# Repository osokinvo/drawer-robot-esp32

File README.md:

# Drawer Robot (esp32)

Этот проект представляет собой робота, который может рисовать простые изображения на плоскости с помощью ESP32.

## 🔧 Особенности

- Управление шаговыми моторами
- Интеграция с FreeRTOS

## 🧩 Используемые технологии

- ESP32 + FreeRTOS
- KiCad для проектирования платы
- 3D-печать корпуса

## 🚀 Установка

1. Скопируйте репозиторий
2. Откройте `firmware/` в PlatformIO или ESP-IDF
3. Скомпилируйте и загрузите на ESP32

## 📂 Структура

- `hardware/pcb/` — разводка и схема платы
- `hardware/3d-models/` — детали корпуса
- `firmware/` — код прошивки
- `docs/` — изображения, схемы

## 📜 Лицензия

Проект распространяется под лицензией MIT.

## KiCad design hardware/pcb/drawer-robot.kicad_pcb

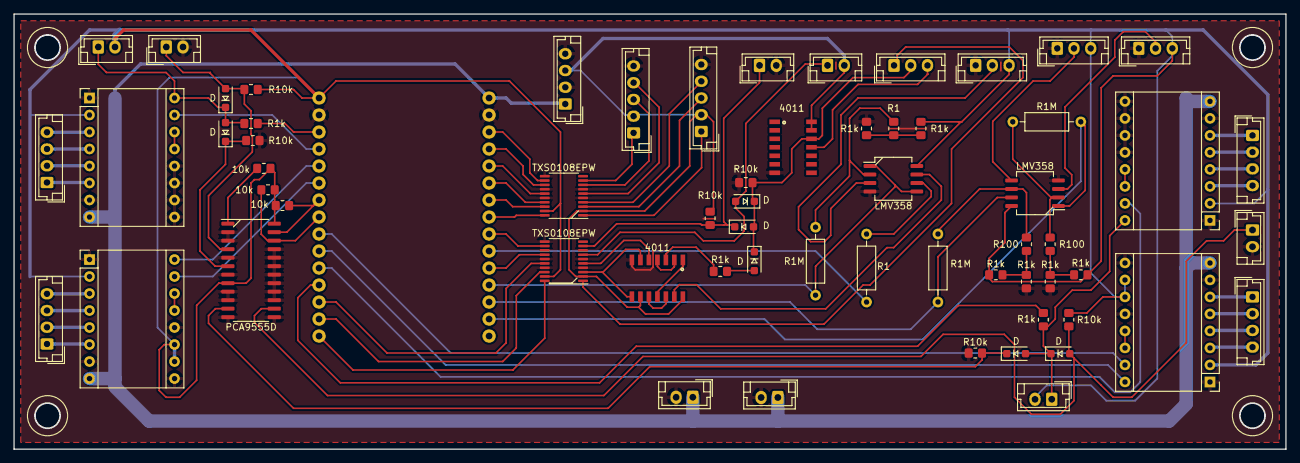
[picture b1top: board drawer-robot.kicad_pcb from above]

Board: 2 copper layers, 190.0 x 65.0 mm, 63 parts (0 on the bottom side), 85 nets.

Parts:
A1, A2, A3, A4: Pololu_Breakout_A4988; Pololu_Breakout-16_15.2x20.3mm
D1, D2, D3, D4, D5, D6, D7: D; D_SOD-123F_dir
J1: ESP32 WROOM DevKit v1
J2, J3, J5, J7, J10: Conn_01x04_Pin; JST_EH_B4B-EH-A_1x04_P2.50mm_Vertical
J4, J6, J8, J9, J11, J12, J22, J23: Conn_01x02_Pin; JST_EH_B2B-EH-A_1x02_P2.50mm_Vertical
J16, J17: Conn_01x05_Pin; JST_EH_B5B-EH-A_1x05_P2.50mm_Vertical
J18, J19, J20, J21: Conn_01x03_Pin; JST_EH_B3B-EH-A_1x03_P2.50mm_Vertical
R1, R3, R30, R31, R34, R35, R38, R39, R42: R1k; R_0805_2012Metric_Pad1.20x1.40mm_HandSolder
R2, R4, R5, R6, R43, R44: R10k; R_0805_2012Metric_Pad1.20x1.40mm_HandSolder
R7: R1; R_Axial_DIN0207_L6.3mm_D2.5mm_P10.16mm_Horizontal
R10, R11, R12: 10k; R_0805_2012Metric_Pad1.20x1.40mm_HandSolder
R32, R36: R100; R_0805_2012Metric_Pad1.20x1.40mm_HandSolder
R33, R37, R41: R1M; R_Axial_DIN0207_L6.3mm_D2.5mm_P10.16mm_Horizontal
R40: R1; R_0805_2012Metric_Pad1.20x1.40mm_HandSolder
U1, U3: LMV358; SO-8_5.3x6.2mm_P1.27mm
U4, U5: 4011; SOP14
U6: PCA9555D; SO-24_5.3x15mm_P1.27mm
U7, U8: TXS0108EPW; TSSOP-20_4.4x6.5mm_P0.65mm

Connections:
+5V: J10.3, J16.2, J17.2, J22.2, R44.2, U4.9, U4.14 (VDD), U5.13, U5.14 (VDD), U7.2 (VCCA), U8.2 (VCCA)
+12V: A1.8 (VMOT), A2.8 (VMOT), A3.8 (VMOT), A4.8 (VMOT), J1.1 (VIN), J10.1, J11.1, J12.1
A1: J1.7 (A9), U7.18 (B2)
A1_10k: J1.14 (VP), R33.1, U1.1
A2: J1.4 (GPIO12), U7.13 (B7)
A2_10k: J1.13 (VN), R37.1, U1.7
AZ_10M: J1.12 (A6), R41.1, U3.1, U3.5 (+)
B1: J1.8 (A8), U7.20 (B1)
B2: J1.3 (GPIO13), U7.12 (B8)
BRAKE_SD1_DIR: J1.18 (GPIO15), R3.1
BRAKE_SD1_STEP: A3.15 (STEP), J1.19 (GPIO2)
BRAKE_SD2_DIR: J1.27 (RX0), R1.1
BRAKE_SD2_STEP: A4.15 (STEP), J1.26 (GPIO21)
Clock2_Pin: J1.23 (GPIO5), R12.1, U6.22 (SCL)
Data2_Pin: J1.22 (TX2), R11.1, U6.23 (SDA)
EN_LOG_Z: J1.29 (GPIO22), U8.18 (B2)
EN_LOG_Z5V: U4.6, U4.8, U8.3 (A2)
FEEDBACK_Z5V: U3.7, U4.13
GND: A1.1 (GND), A1.7 (GND), A1.9 (~ENABLE), A1.12 (MS3), A2.1 (GND), A2.7 (GND), A2.9 (~ENABLE), A2.12 (MS3), A3.1 (GND), A3.7 (GND), A3.9 (~ENABLE), A3.10 (MS1), A3.11 (MS2), A3.12 (MS3), A4.1 (GND), A4.7 (GND), A4.9 (~ENABLE), A4.10 (MS1), A4.11 (MS2), A4.12 (MS3), J1.2 (GND), J1.17 (GND), J6.2, J9.2, J10.2, J10.4, J11.2, J12.2, J16.5, J17.5, J18.1, J19.1, J20.1, J23.2, R2.2, R5.2, R31.1, R35.1, R39.1, R43.2, U1.4 (V-), U3.4 (V-), U4.7 (VSS), U5.7 (VSS), U6.2 (A1), U6.3 (A2), U6.5 (IO0_1), U6.7 (IO0_3), U6.9 (IO0_5), U6.10 (IO0_6), U6.12 (VSS), U6.13 (IO1_0), U6.15 (IO1_2), U6.16 (IO1_3), U6.17 (IO1_4), U6.18 (IO1_5), U6.19 (IO1_6), U6.20 (IO1_7), U6.21 (A0), U7.5 (A4), U7.7 (A6), U7.11 (GND), U7.14 (B6), U7.16 (B4), U8.4 (A3), U8.6 (A5), U8.8 (A7), U8.11 (GND), U8.13 (B7), U8.15 (B5), U8.17 (B3)
LOG_AZ_10M: J1.10 (A4), R7.1
LOG_Z5V: U4.5, U8.5 (A4)
LOG_Z_DIR: J1.28 (TX0), U8.16 (B4)
unnamed: A1.4 (1A), J5.3
unnamed: A1.3 (1B), J5.4
unnamed: A1.5 (2A), J5.2
unnamed: A1.6 (2B), J5.1
unnamed: A1.13 (~RESET), A1.14 (~SLEEP)
unnamed: A2.4 (1A), J2.3
unnamed: A2.3 (1B), J2.4
unnamed: A2.5 (2A), J2.2
unnamed: A2.6 (2B), J2.1
unnamed: A2.13 (~RESET), A2.14 (~SLEEP)
unnamed: A3.4 (1A), J7.3
unnamed: A3.3 (1B), J7.4
unnamed: A3.5 (2A), J7.2
unnamed: A3.6 (2B), J7.1
unnamed: A3.16 (DIR), D1.1 (K), D3.2 (A), J8.1, R3.2
unnamed: A3.13 (~RESET), A3.14 (~SLEEP)
unnamed: A4.4 (1A), J3.3
unnamed: A4.3 (1B), J3.4
unnamed: A4.5 (2A), J3.2
unnamed: A4.6 (2B), J3.1
unnamed: A4.16 (DIR), D5.2 (A), D7.1 (K), J4.1, R1.2
unnamed: A4.13 (~RESET), A4.14 (~SLEEP)
unnamed: D2.2 (A), D4.1 (K), D6.1 (K), J21.2, R43.1, U5.12
unnamed: D4.2 (A), R42.2
unnamed: J16.1, U7.1 (A1)
unnamed: J16.3, U7.3 (A2)
unnamed: J16.4, U7.4 (A3)
unnamed: J17.1, U7.9 (A8)
unnamed: J17.3, U7.8 (A7)
unnamed: J17.4, U7.6 (A5)
unnamed: J18.2, U1.3 (+)
unnamed: J19.2, U1.5 (+)
unnamed: J20.2, U3.3 (+)
unnamed: J21.3, U5.11
unnamed: R30.1, R31.2, R32.2
unnamed: R34.1, R35.2, R36.2
unnamed: R38.1, R39.2, R40.2
unnamed: R32.1, R33.2, U1.2 (-)
unnamed: R36.1, R37.2, U1.6 (-)
unnamed: R40.1, R41.2, U3.2 (-)
unnamed: R7.2, U3.6 (-)
unnamed: U4.1, U4.11
unnamed: U4.2, U4.4
unnamed: U4.10, U4.12
SD1_DIR: A1.16 (DIR), J1.20 (GPIO4)
SD1_STEP: A1.15 (STEP), J1.21 (RX2)
SD2_DIR: A2.16 (DIR), J1.25 (GPIO19)
SD2_STEP: A2.15 (STEP), J1.24 (GPIO18)
STOP_SD1_MAX: D3.1 (K), R5.1, U6.6 (IO0_2)
STOP_SD1_MIN: D1.2 (A), J9.1, R4.1, U6.4 (IO0_0)
STOP_SD2_MAX: D5.1 (K), R2.1, U6.11 (IO0_7)
STOP_SD2_MIN: D7.2 (A), J6.1, R6.1, U6.14 (IO1_1)
STOP_Z_MAX: J1.9 (A5), U8.12 (B8)
STOP_Z_MAX5V: D6.2 (A), J22.1, U8.7 (A6)
STOP_Z_MIN: J1.11 (A7), U8.14 (B6)
STOP_Z_MIN5V: D2.1 (K), J23.1, R44.1, U8.9 (A8)
VDD3V3: A1.2 (VDD), A1.10 (MS1), A1.11 (MS2), A2.2 (VDD), A2.10 (MS1), A2.11 (MS2), A3.2 (VDD), A4.2 (VDD), J1.16 (VDD3V3), J4.2, J8.2, J18.3, J19.3, J20.3, R4.2, R6.2, R10.2, R11.2, R12.2, R30.2, R34.2, R38.2, U1.8 (V+), U3.8 (V+), U6.8 (IO0_4), U6.24 (VDD), U7.19 (VCCB), U8.19 (VCCB)
X1: J1.6 (GPIO27), U7.17 (B3)
X2: J1.5 (GPIO14), U7.15 (B5)
Z_DIR: R42.1, U4.3
Z_VEL: J1.30 (GPIO23), U8.20 (B1)
Z_VEL5V: J21.1, U8.1 (A1)
~INT2: R10.1, U6.1 (~INT)

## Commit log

2025-06-22 add control board
2025-06-23 Add component list
2025-06-29 Created functional file
2025-07-05 Add function for brake motor
2025-07-13 Add function with motor and encoder
2025-07-20 Add encoder functions
2025-07-27 Add wifi function
2025-08-03 Add Websocket
2025-09-25 Run server
